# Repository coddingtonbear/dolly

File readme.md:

# Dolly

Dolly is a GRBL controller board that my existing "Woodpecker" GRBL controller board
will make for me.  It includes a few features that my CNC machine's stock
board did not offer including:

* JST-XH connectors for spindle, probe, and end stop connections.
* Bluetooth connectivity via an on-board HC-05 module.
* On-Board ICSP header to allow for reflashing without using USB Bootloader.

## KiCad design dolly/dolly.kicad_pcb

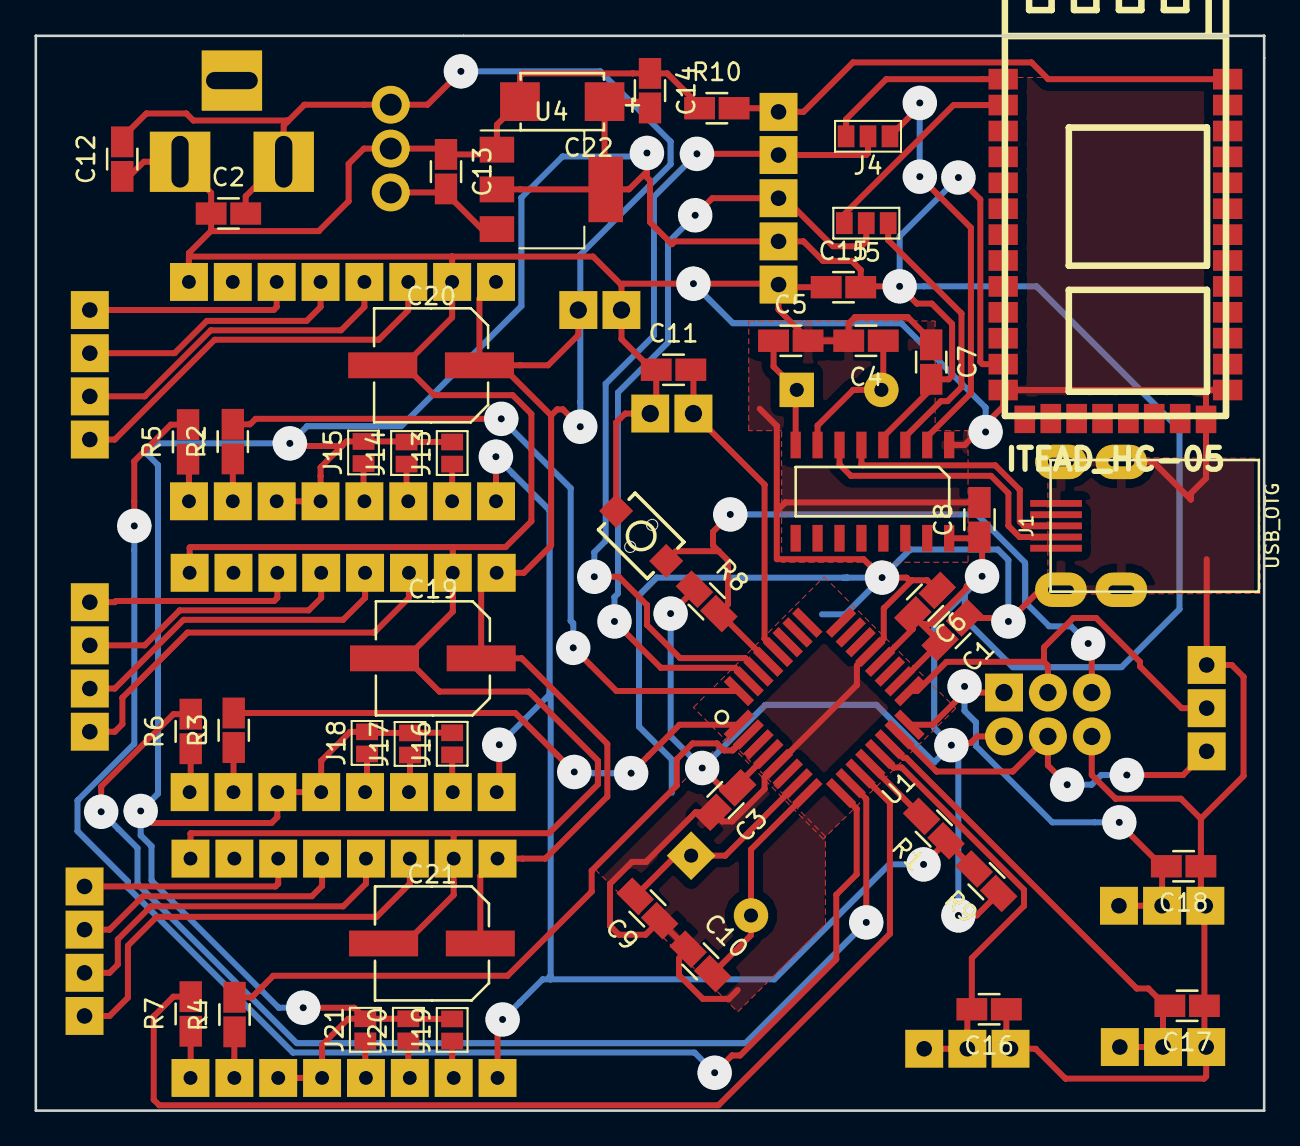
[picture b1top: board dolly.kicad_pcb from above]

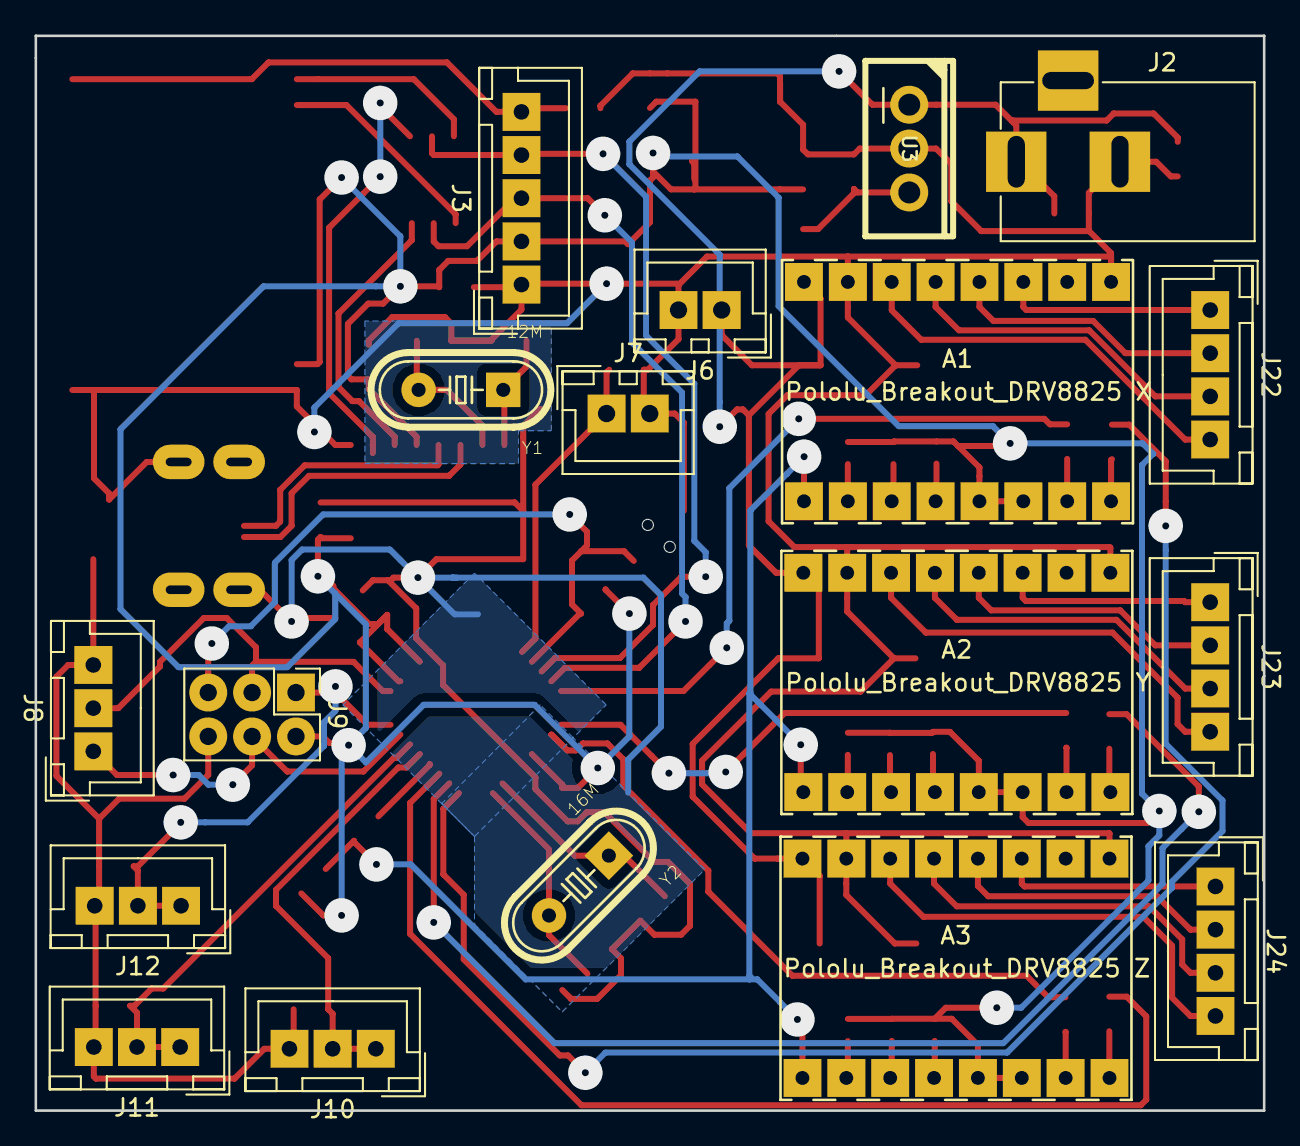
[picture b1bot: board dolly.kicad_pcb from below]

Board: 2 copper layers, 71.1 x 62.2 mm, 67 parts (18 on the bottom side), 59 nets.

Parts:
A1: Pololu_Breakout_DRV8825 X; Pololu_Stepper_Breakout
A2: Pololu_Breakout_DRV8825 Y; Pololu_Stepper_Breakout
A3: Pololu_Breakout_DRV8825 Z; Pololu_Stepper_Breakout
C1, C2, C3, C6, C7, C8, C11, C14, C15, C16, C17, C18: 0.1u; 0805_Milling
C4, C5, C9, C10: 22p; 0805_Milling
C12, C13: 0.33u; 0805_Milling
C19, C20, C21: 100u; CAP-SMD-SIZE-D
C22: 220u; CAPACITOR_TANTALUM_C
J1: USB_OTG; UJ2-MIBH-4-SMT
J2: Barrel_Jack; BARREL_JACK
J3: UART; JST_XH_B05B-XH-A_05x2.50mm_Straight_LargePads
J4: RX; GS3
J5: TX; GS3
J6: 24V_Out; JST_XH_B02B-XH-A_02x2.50mm_Straight_LargePads
J7: Probe; JST_XH_B02B-XH-A_02x2.50mm_Straight_LargePads
J8: Spindle; JST_XH_B03B-XH-A_03x2.50mm_Straight_LargePads
J9: ICSP; Pin_Header_Straight_2x03_Pitch2.54mm
J10: X_End; JST_XH_B03B-XH-A_03x2.50mm_Straight_LargePads
J11: Y_End; JST_XH_B03B-XH-A_03x2.50mm_Straight_LargePads
J12: Z_End; JST_XH_B03B-XH-A_03x2.50mm_Straight_LargePads
J13, J14, J15, J16, J17, J18, J19, J20, J21: GS2
J22: X_Stepper; JST_XH_B04B-XH-A_04x2.50mm_Straight_LargePads
J23: Y_Stepper; JST_XH_B04B-XH-A_04x2.50mm_Straight_LargePads
J24: Z_Stepper; JST_XH_B04B-XH-A_04x2.50mm_Straight_LargePads
R1, R2, R3, R4, R5, R6, R7: 100; 0805_Milling
R8, R9, R10: 10k; 0805_Milling
SW1: SW_SPST; SW_PUSHBUTTON_TINY_2PIN
U1: ATMEGA328PB-AU; TQFP32_ATMEGA328P
U2: CH340G; SOIC-16
U3: L7805; TO-220
U4: AP1117-15; SOT-223-3Lead_TabPin2
U5: ITEAD_HC-05
Y1: 12M; XTAL_HC-49US-16.000MHZ
Y2: 16M; XTAL_HC-49US-16.000MHZ

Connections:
+3V3: A1.13, A1.14, A2.13, A2.14, A3.13, A3.14, C1.2, C3.1, C6.2, C7.2, C8.1, C14.2, C15.2, C22.1, J3.2, J9.2, J13.2, J14.2, J15.2, J16.2, J17.2, J18.2, J19.2, J20.2, J21.2, R8.1, R9.1, U1.4, U1.18, U1.20, U2.4, U2.16, U4.2, U5.12
+24V: A1.8, A2.8, A3.8, C2.2, C12.2, C19.1, C20.1, C21.1, J2.1, J6.1, U3.1
BT_IN: J5.1, U5.2
BT_KEY: J3.5, R10.2, U5.34
BT_OUT: J4.1, U5.1
GND: A1.1, A1.7, A2.1, A2.7, A3.1, A3.7, C1.1, C2.1, C3.2, C4.2, C5.2, C6.1, C7.1, C8.2, C9.1, C10.1, C11.1, C12.1, C13.1, C14.1, C15.1, C16.1, C17.1, C18.1, C19.2, C20.2, C21.2, C22.2, J1.5, J1.6, J2.2, J3.1, J6.2, J7.2, J8.3, J9.6, J10.3, J11.3, J12.3, R10.1, SW1.2, U1.5, U1.21, U2.1, U3.2, U4.1, U5.13, U5.21, U5.22
MISO: C18.2, J9.1, J12.1, J12.2, U1.16
MOSI: J8.1, J9.4, U1.15
unnamed: A1.3, J22.1
unnamed: A1.4, J22.2
unnamed: A1.5, J22.3
unnamed: A1.6, J22.4
unnamed: A1.10, J13.1
unnamed: A1.11, J14.1
unnamed: A1.12, J15.1
unnamed: A2.3, J23.1
unnamed: A2.4, J23.2
unnamed: A2.5, J23.3
unnamed: A2.6, J23.4
unnamed: A2.10, J16.1
unnamed: A2.11, J17.1
unnamed: A2.12, J18.1
unnamed: A3.3, J24.1
unnamed: A3.4, J24.2
unnamed: A3.5, J24.3
unnamed: A3.6, J24.4
unnamed: A3.10, J19.1
unnamed: A3.11, J20.1
unnamed: A3.12, J21.1
unnamed: C4.1, U2.7, Y1.2
unnamed: C5.1, U2.8, Y1.1
unnamed: C9.2, U1.7, Y2.1
unnamed: C10.2, U1.8, Y2.2
unnamed: C13.2, U3.3, U4.3
unnamed: J1.2, U2.6
unnamed: J1.3, U2.5
unnamed: R1.2, U1.12
unnamed: R2.2, U1.32
unnamed: R3.2, U1.1
unnamed: R4.2, U1.2
unnamed: R5.2, U1.9
unnamed: R6.2, U1.10
unnamed: R7.2, U1.11
PROBE: C11.2, J7.1, U1.28
RST: J9.5, R8.2, SW1.1, U1.29
RX: J3.4, J4.2, U1.30
SCK: J8.2, J9.3, U1.17
TX: J3.3, J5.2, U1.31
USB_IN: J5.3, U2.3
USB_OUT: J4.3, U2.2
XDIR: A1.16, R5.1
XEND: C16.2, J10.1, J10.2, U1.13
XSTEP: A1.15, R2.1
YDIR: A2.16, R6.1
YEND: C17.2, J11.1, J11.2, U1.14
YSTEP: A2.15, R3.1
ZDIR: A3.16, R7.1
ZSTEP: A3.15, R4.1
~ENABLE_STEPPER: A1.9, A2.9, A3.9, R1.1, R9.2

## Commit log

2018-03-18 And so it begins...
2018-03-18 Adding readme.
2018-03-18 Adding errata and future ideas sections.
2018-03-25 Adding optional 0.1uF capacitors between spindle direction/pwm pins and gnd.
